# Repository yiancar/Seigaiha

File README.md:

Seigaiha
================

This Alice layout keyboard kit is made using ONLY through hole components and inspired by the [Plaid](https://github.com/hsgw/plaid) and [TGR Alice](https://geekhack.org/index.php?topic=95054.0).

Atmega328p with VUSB on [QMK firmware](https://github.com/qmk/qmk_firmware).

To alter the pcb use KiCAD V5.0 or newer as it already contains most of the libraries. The additional libraries are provided.

License
===========

This project is licensed under the [Creative Commons Attribution-NonCommercial 4.0 International License](https://creativecommons.org/licenses/by-nc/4.0/).

If you have remixed, adapted or build upon this work and wish to remove the non-commercial clause for your own project please contact me at https://www.yiancar-designs.com. Your request is more than likely to be granted. The non-commercial part of the license is intended to avoid direct copies of the work to be sold for commercial gain by third parties.

The USB4085-GF-A footprint, symbol and 3D model are licensed under [Attribution-ShareAlike 4.0 International](https://creativecommons.org/licenses/by-sa/4.0/). Originally created by [SnapEDA](https://snapeda.com). The footprint has been modified to increase the hole size of the shield pads.

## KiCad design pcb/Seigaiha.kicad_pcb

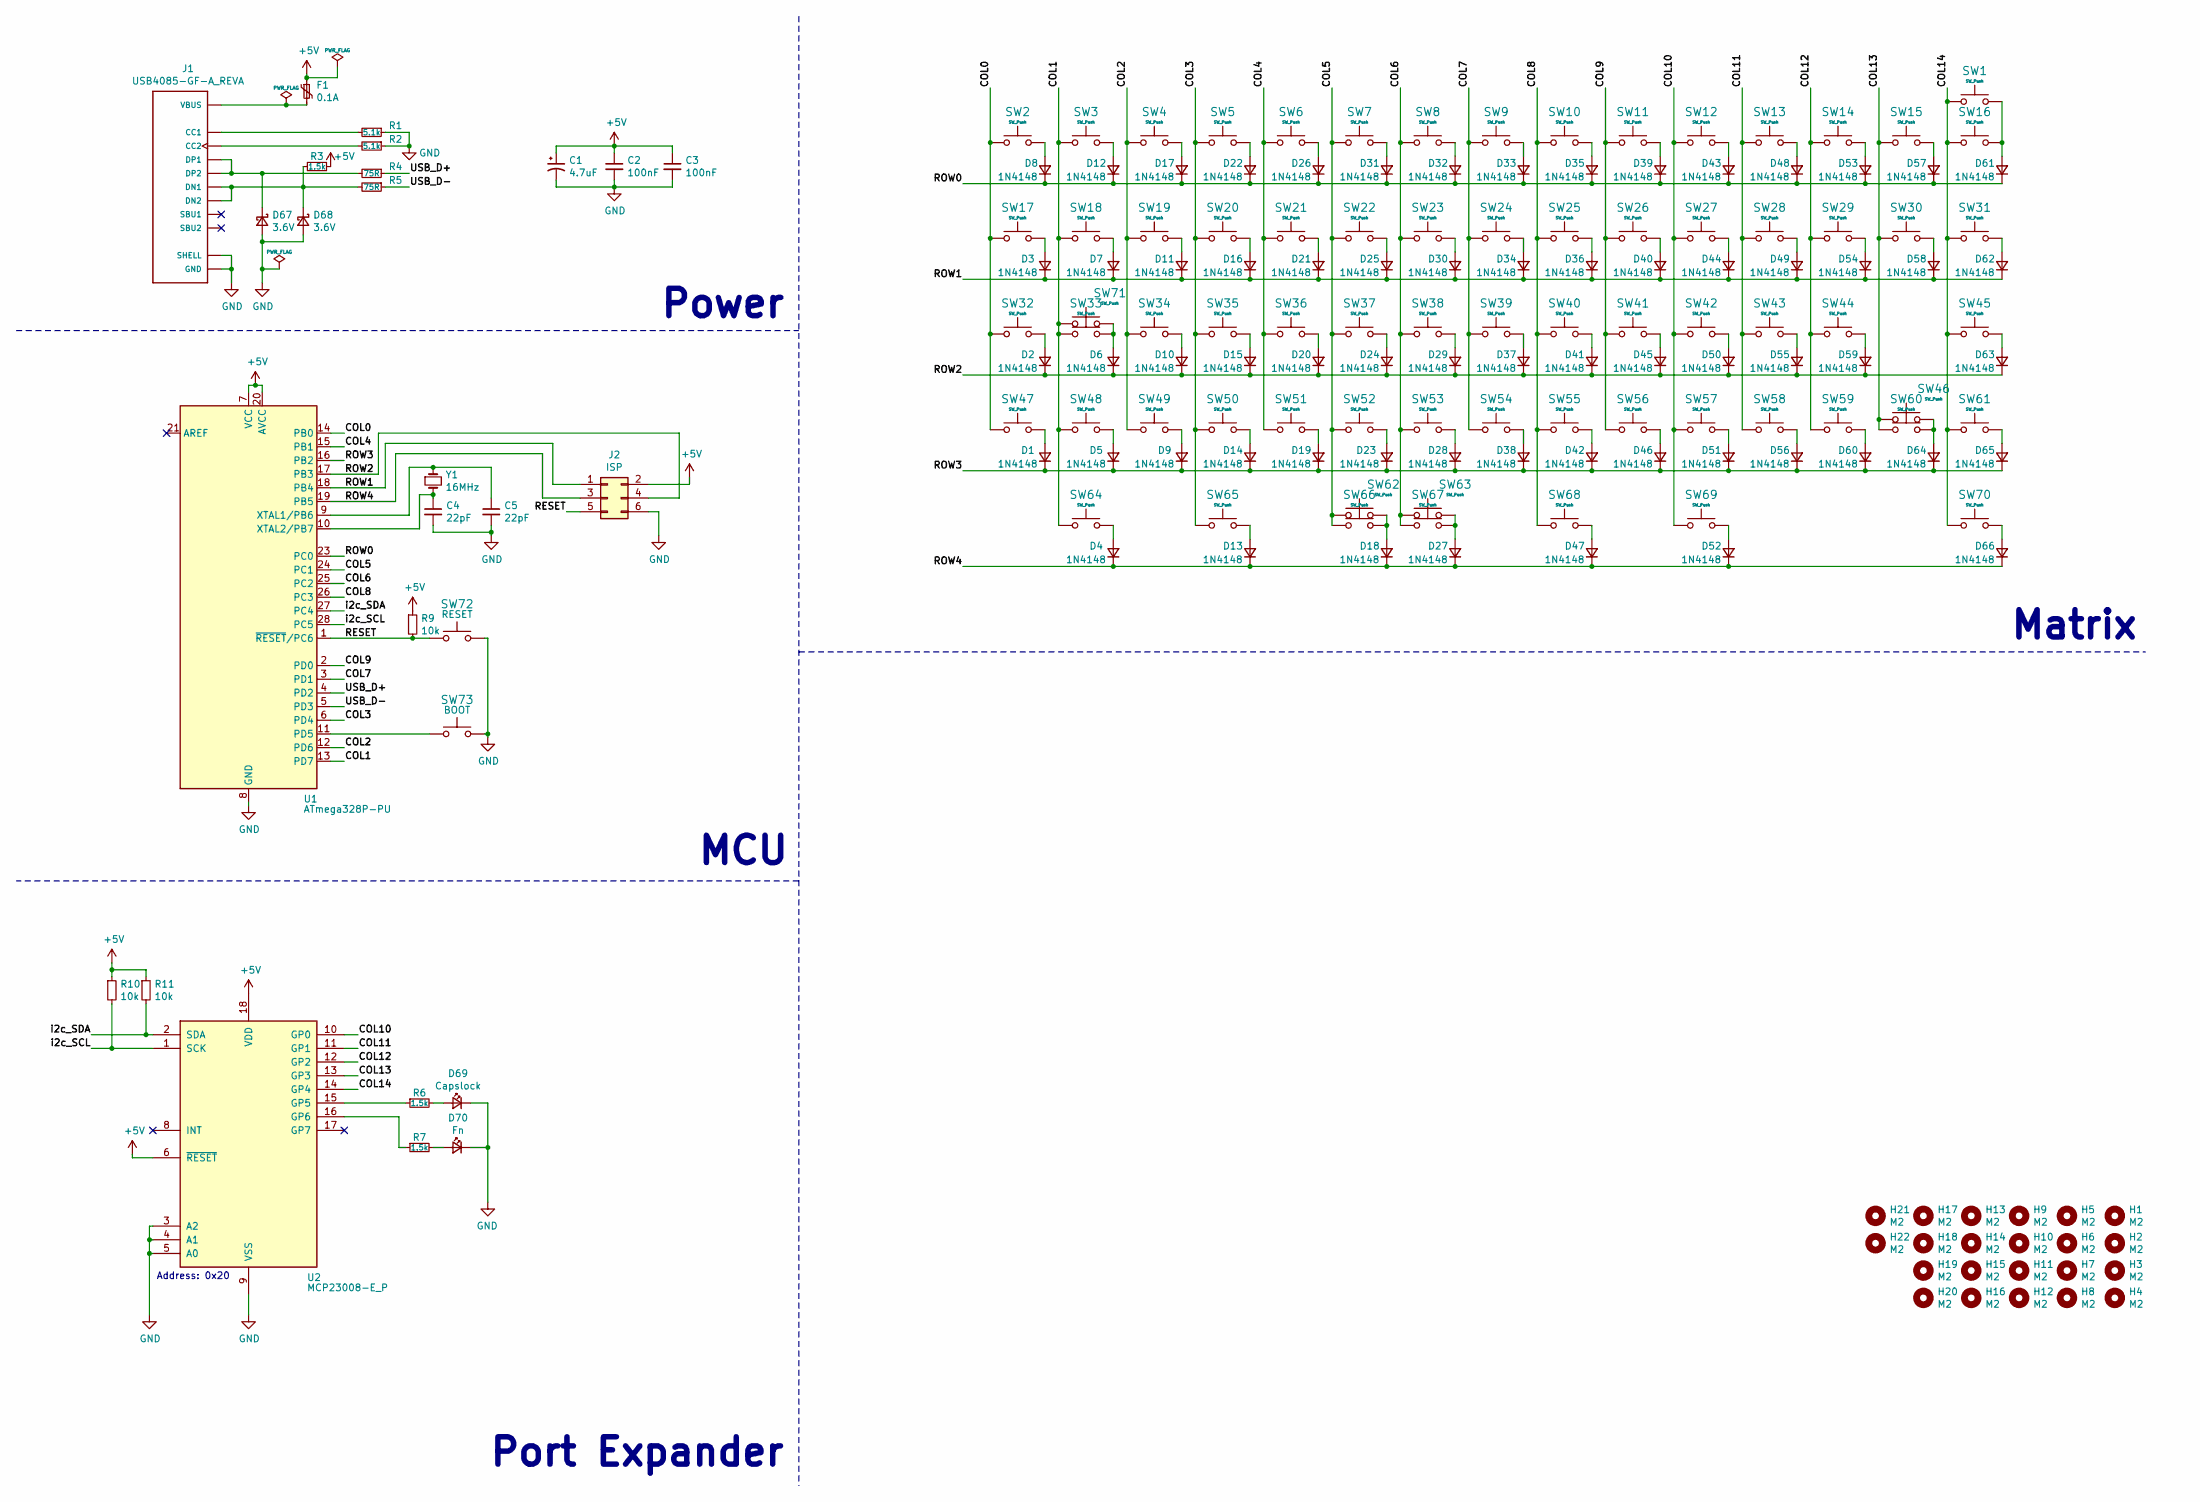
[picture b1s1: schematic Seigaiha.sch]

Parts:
C1: 4.7uF; CP_Radial_D4.0mm_P1.50mm
C2, C3: 100nF; C_Disc_D4.3mm_W1.9mm_P5.00mm
C4, C5: 22pF; C_Disc_D4.3mm_W1.9mm_P5.00mm
D1, D2, D3, D4, D5, D6, D7, D8, D9, D10, D11, D12, D13, D14, D15, D16, D17, D18, D19, D20, D21, D22, D23, D24, D25, D26, D27, D28, D29, D30, D31, D32, D33, D34, D35, D36, D37, D38, D39, D40, D41, D42, D43, D44, D45, D46, D47, D48, D49, D50, D51, D52, D53, D54, D55, D56, D57, D58, D59, D60, D61, D62, D63, D64, D65, D66: 1N4148; D_DO-35_SOD27_P7.62mm_Horizontal
D67, D68: 3.6V; D_DO-35_SOD27_P7.62mm_Horizontal
D69: Capslock; LED_D3.0mm_Clear
D70: Fn; LED_D3.0mm_Clear
F1: 0.1A; C_Disc_D5.0mm_W2.5mm_P5.00mm
H1, H2, H3, H4, H5, H6, H7, H8, H9, H10, H11, H12, H13, H14, H15, H16, H17, H18, H19, H20, H21, H22: M2; MountingHole_2.2mm_M2_DIN965_Pad
J1: USB4085-GF-A_REVA; GCT_USB4085-GF-A_REVA
J2: ISP; PinHeader_2x03_P2.54mm_Vertical
R1, R2: 5.1k; R_Axial_DIN0204_L3.6mm_D1.6mm_P5.08mm_Horizontal
R3, R6, R7: 1.5k; R_Axial_DIN0204_L3.6mm_D1.6mm_P5.08mm_Horizontal
R4, R5: 75R; R_Axial_DIN0204_L3.6mm_D1.6mm_P5.08mm_Horizontal
R9, R10, R11: 10k; R_Axial_DIN0204_L3.6mm_D1.6mm_P5.08mm_Horizontal
SW1, SW2, SW3, SW4, SW5, SW6, SW7, SW8, SW9, SW10, SW11, SW12, SW13, SW14, SW15, SW17, SW19, SW20, SW21, SW22, SW23, SW24, SW25, SW26, SW27, SW28, SW29, SW30, SW32, SW34, SW35, SW36, SW37, SW38, SW39, SW40, SW41, SW42, SW43, SW44, SW47, SW49, SW50, SW51, SW52, SW53, SW54, SW55, SW56, SW57, SW58, SW59, SW61, SW67: SW_Push; MX-1U-NoLED
SW16: SW_Push; MX-2U-NoLED
SW18, SW31, SW64, SW65, SW69, SW70: SW_Push; MX-1.5U-NoLED
SW33, SW46: SW_Push; MX-1.75U-NoLED
SW45, SW62: SW_Push; MX-2.25U-ReversedStabilizers-NoLED
SW48: SW_Push; MX-2.25U-NoLED
SW60: SW_Push; MX-2.75U-NoLED
SW63, SW71: SW_Push; MX-1.25U-NoLED
SW66: SW_Push; MX-2U-ReversedStabilizers-NoLED
SW68: SW_Push; MX-2.75U-ReversedStabilizers-NoLED
SW72: RESET; SW_PUSH_6mm
SW73: BOOT; SW_PUSH_6mm
U1: ATmega328P-PU; DIP-28_W7.62mm
U2: MCP23008-E_P; DIP-18_W7.62mm
Y1: 16MHz; Crystal_HC49-4H_Vertical

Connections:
+5V: C1.1, C2.1, C3.1, F1.1, J2.2, R3.1, R9.1, R10.1, R11.1, U1.7 (VCC), U1.20 (AVCC), U2.6 (~RESET~), U2.18 (VDD)
/COL0: SW2.2, SW17.2, SW32.2, SW47.2, U1.14 (PB0)
/COL1: SW3.2, SW18.2, SW33.2, SW48.2, SW64.2, SW71.2, U1.13 (PD7)
/COL2: SW4.2, SW19.2, SW34.2, SW49.2, U1.12 (PD6)
/COL3: SW5.2, SW20.2, SW35.2, SW50.2, SW65.2, U1.6 (PD4)
/COL4: SW6.2, SW21.2, SW36.2, SW51.2, U1.15 (PB1)
/COL5: SW7.2, SW22.2, SW37.2, SW52.2, SW62.2, SW66.2, U1.24 (PC1)
/COL6: SW8.2, SW23.2, SW38.2, SW53.2, SW63.2, SW67.2, U1.25 (PC2)
/COL7: SW9.1, SW24.1, SW39.1, SW54.1, U1.3 (PD1)
/COL8: SW10.1, SW25.1, SW40.1, SW55.1, SW68.1, U1.26 (PC3)
/COL9: SW11.1, SW26.1, SW41.1, SW56.1, U1.2 (PD0)
/COL10: SW12.1, SW27.1, SW42.1, SW57.1, SW69.1, U2.10 (GP0)
/COL11: SW13.1, SW28.1, SW43.1, SW58.1, U2.11 (GP1)
/COL12: SW14.1, SW29.1, SW44.1, SW59.1, U2.12 (GP2)
/COL13: SW15.1, SW30.1, SW46.1, SW60.1, U2.13 (GP3)
/COL14: SW1.1, SW16.1, SW31.1, SW45.1, SW61.1, SW70.1, U2.14 (GP4)
/RESET: J2.5, R9.2, SW72.2, U1.1 (~RESET~/PC6)
/ROW0: D8.1 (K), D12.1 (K), D17.1 (K), D22.1 (K), D26.1 (K), D31.1 (K), D32.1 (K), D33.1 (K), D35.1 (K), D39.1 (K), D43.1 (K), D48.1 (K), D53.1 (K), D57.1 (K), D61.1 (K), U1.23 (PC0)
/ROW1: D3.1 (K), D7.1 (K), D11.1 (K), D16.1 (K), D21.1 (K), D25.1 (K), D30.1 (K), D34.1 (K), D36.1 (K), D40.1 (K), D44.1 (K), D49.1 (K), D54.1 (K), D58.1 (K), D62.1 (K), J2.1, U1.18 (PB4)
/ROW2: D2.1 (K), D6.1 (K), D10.1 (K), D15.1 (K), D20.1 (K), D24.1 (K), D29.1 (K), D37.1 (K), D41.1 (K), D45.1 (K), D50.1 (K), D55.1 (K), D59.1 (K), D63.1 (K), J2.4, U1.17 (PB3)
/ROW3: D1.1 (K), D5.1 (K), D9.1 (K), D14.1 (K), D19.1 (K), D23.1 (K), D28.1 (K), D38.1 (K), D42.1 (K), D46.1 (K), D51.1 (K), D56.1 (K), D60.1 (K), D64.1 (K), D65.1 (K), U1.16 (PB2)
/ROW4: D4.1 (K), D13.1 (K), D18.1 (K), D27.1 (K), D47.1 (K), D52.1 (K), D66.1 (K), J2.3, U1.19 (PB5)
/USB_D+: R4.1, U1.4 (PD2)
/USB_D-: R5.1, U1.5 (PD3)
/i2c_SCL: R10.2, U1.28 (PC5), U2.1 (SCK)
/i2c_SDA: R11.2, U1.27 (PC4), U2.2 (SDA)
GND: C1.2, C2.2, C3.2, C4.2, C5.2, D67.2 (A), D68.2 (A), D69.1 (K), D70.1 (K), J1.A1 (GND), J1.A12 (GND), J1.B1 (GND), J1.B12 (GND), J1.P1 (SHELL), J1.P2 (SHELL), J1.P3 (SHELL), J1.P4 (SHELL), J2.6, R1.1, R2.1, SW72.1, SW73.1, U1.8 (GND), U1.22 (GND), U2.3 (A2), U2.4 (A1), U2.5 (A0), U2.9 (VSS)
unnamed: C4.1, U1.10 (XTAL2/PB7), Y1.2
unnamed: C5.1, U1.9 (XTAL1/PB6), Y1.1
unnamed: D1.2 (A), SW47.1
unnamed: D2.2 (A), SW32.1
unnamed: D3.2 (A), SW17.1
unnamed: D4.2 (A), SW64.1
unnamed: D5.2 (A), SW48.1
unnamed: D6.2 (A), SW33.1, SW71.1
unnamed: D7.2 (A), SW18.1
unnamed: D8.2 (A), SW2.1
unnamed: D9.2 (A), SW49.1
unnamed: D10.2 (A), SW34.1
unnamed: D11.2 (A), SW19.1
unnamed: D12.2 (A), SW3.1
unnamed: D13.2 (A), SW65.1
unnamed: D14.2 (A), SW50.1
unnamed: D15.2 (A), SW35.1
unnamed: D16.2 (A), SW20.1
unnamed: D17.2 (A), SW4.1
unnamed: D18.2 (A), SW62.1, SW66.1
unnamed: D19.2 (A), SW51.1
unnamed: D20.2 (A), SW36.1
unnamed: D21.2 (A), SW21.1
unnamed: D22.2 (A), SW5.1
unnamed: D23.2 (A), SW52.1
unnamed: D24.2 (A), SW37.1
unnamed: D25.2 (A), SW22.1
unnamed: D26.2 (A), SW6.1
unnamed: D27.2 (A), SW63.1, SW67.1
unnamed: D28.2 (A), SW53.1
unnamed: D29.2 (A), SW38.1
unnamed: D30.2 (A), SW23.1
unnamed: D31.2 (A), SW7.1
unnamed: D32.2 (A), SW8.1
unnamed: D33.2 (A), SW9.2
unnamed: D34.2 (A), SW24.2
unnamed: D35.2 (A), SW10.2
unnamed: D36.2 (A), SW25.2
unnamed: D37.2 (A), SW39.2
unnamed: D38.2 (A), SW54.2
unnamed: D39.2 (A), SW11.2
unnamed: D40.2 (A), SW26.2
unnamed: D41.2 (A), SW40.2
unnamed: D42.2 (A), SW55.2
unnamed: D43.2 (A), SW12.2
unnamed: D44.2 (A), SW27.2
unnamed: D45.2 (A), SW41.2
unnamed: D46.2 (A), SW56.2
unnamed: D47.2 (A), SW68.2
unnamed: D48.2 (A), SW13.2
unnamed: D49.2 (A), SW28.2
unnamed: D50.2 (A), SW42.2
unnamed: D51.2 (A), SW57.2
unnamed: D52.2 (A), SW69.2
unnamed: D53.2 (A), SW14.2
unnamed: D54.2 (A), SW29.2
unnamed: D55.2 (A), SW43.2
unnamed: D56.2 (A), SW58.2
unnamed: D57.2 (A), SW15.2
unnamed: D58.2 (A), SW30.2
unnamed: D59.2 (A), SW44.2
unnamed: D60.2 (A), SW59.2
unnamed: D61.2 (A), SW1.2, SW16.2
unnamed: D62.2 (A), SW31.2
unnamed: D63.2 (A), SW45.2
unnamed: D64.2 (A), SW46.2, SW60.2
unnamed: D65.2 (A), SW61.2
unnamed: D66.2 (A), SW70.2
unnamed: D67.1 (K), J1.A6 (DP1), J1.B6 (DP2), R4.2
unnamed: D68.1 (K), J1.A7 (DN1), J1.B7 (DN2), R3.2, R5.2
unnamed: D69.2 (A), R6.2
unnamed: D70.2 (A), R7.2
unnamed: F1.2, J1.A4 (VBUS), J1.A9 (VBUS), J1.B4 (VBUS), J1.B9 (VBUS)
unnamed: J1.A5 (CC1), R1.2
unnamed: J1.B5 (CC2), R2.2
unnamed: R6.1, U2.15 (GP5)
unnamed: R7.1, U2.16 (GP6)
unnamed: SW73.2, U1.11 (PD5)

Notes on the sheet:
Address: 0x20
Power
MCU
Port Expander
Matrix

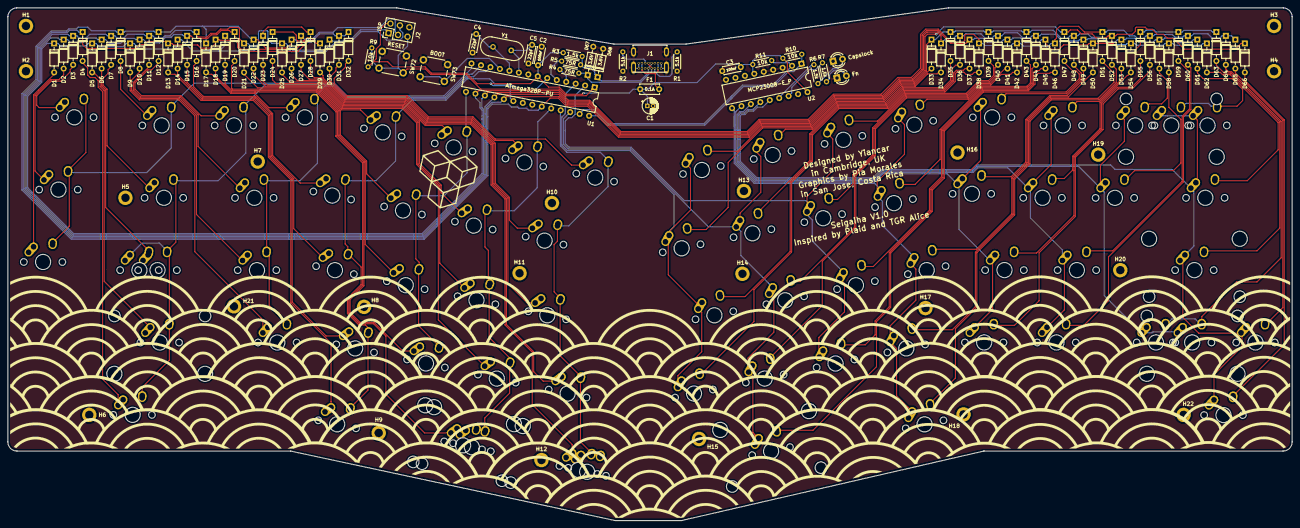
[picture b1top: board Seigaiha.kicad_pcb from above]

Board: 2 copper layers, 338.1 x 135.0 mm, 187 parts (0 on the bottom side), 105 nets.

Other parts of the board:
Ref**: Val**; seigaiha_logo

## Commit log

2021-09-12 Upload Instructions
2021-10-22 initial
2021-10-22 Add PCB

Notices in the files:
README.md:
cc-by-nc
